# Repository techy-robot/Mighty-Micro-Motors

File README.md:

# Mighty Micro Motors
My goal with this project is to recreate the expensive and highly advanced motors typically found in big robots, such as in Boston Dynamics or MIT's robots, but at a **much** smaller scale. These are essentially tiny drone motors with a high reduction gearbox, a magnetic encoder, and a FOC controller board.

You can check out my project log [here](Progress%20Log.md).

This project is sponsored by [PCBWay](https://www.pcbway.com/)

## Gearbox
This has to be a resin printed or precision machined gearbox, just from the sheer smallness of everything. The brushless drone motors (HappyModel SE0802) are 10mm in diameter, so the gearbox ideally should be a similar size.

I'm currently thinking about having a cycloidal or split-ring planetary gearbox, due to the compact size and high reduction ratios

Preliminary CAD designs are on onshape, you can watch my progress here: [Mighty Micro Motors - Onshape](https://cad.onshape.com/documents/c861ec30af8169cf9c14bd7f/w/e538486c85e6a5fe77cd1d33/e/19bd07544dbaacbeb2fafd06). Step files and STL files will also be uploaded to this repo.

### Cycloidal 16-to-1 reduction:

Currently the design is twice as big as my ideal, with a 19mm diameter. I can not reduce the diameter without removing the bearings, possible reducing the lifespan. This *really* needs to be smaller, so I may do some testing and just remove some bearings. I'm not actually sure how well the 1x3x1mm bearings roll compared to just a smooth shaft. I could also cut the hole count down if the screws were also the shafts.

In real life:

### Split Ring Compound Planetary gearbox 74.66-to-1 reduction:

This goes by a variety of names, but basically this is a two-stage planetary gearbox, with the planets merged together. Due to some interesting mechanics, this type of gearbox can have **an extreme** reduction ratio in a relatively small size. The reduction ratio is the first stage ratio(ring teeth / sun teeth) multiplied by 2nd stage ring teeth, divided by the number of planets (simplified, this only works if both planet gear sets have the same number of teeth). The 2nd stage is advanced by a few teeth every revolution of the first. This operates on the same principle as a cycloidal drive and a harmonic drive, but with the added reduction ratio of the planetary gears, and without the vibration.

One thing to note with this type of gearbox is that the output encoder wires cannot fit through the center like my other gearbox, which limits the usable motion range to 270 degrees.

My particular version is a 74.66:1, in a much smaller form-factor than my cycloidal drive!

## Control board
### Version 1
My first version of the control board is designed to test all functions that may exist on a robot. I have the motor driver, a MCU for the algorithms, connectors for sensors (I2c and SPI), and a power management system.

A lot of care has been taken to design for EMI, which is why I have separate ground planes and have plotted current return paths for *most* traces. When I design a controller that supports 3+ motors I'm going to deal with length matching too on the low speed signals (Currently I'm testing all possible pin combinations, which doesn't lend itself to length matching). I'm still learning about good EMI design practices though, so there may be a big flaw in the design I don't see.

At it's current state the control PCB has been assembled and power tested. Nothing blew up or heated up, though I have discovered that the battery protection chip is not working. I will probably just bypass that circuit and move on.

[Schematic](Media/stm32g070%20and%20DRV8311%20single%20motor%20board%20-%20V1%20Alpha.pdf)

**Specs:**
- TI BQ25060 single-cell battery charger along with a BQ298012 battery protection chip. 
- 4 mosfets on board to control system power, 60+ amps of current
- TI DRV8311 motor driver, which can drive a brushless motor at 5 amps current (I fully expect heat problems due to the small size of the chip!)
- STM32G070CB, clocked at the max 64mhz (16mhz crystal scaled internally). 128kb mem, 64kb ram. The stm32 I chose is relatively inexpensive and *should be able to handle 3 motors*. (this was proven false later after testing other MCUs)

The motor driver section is 16x11mm, which hopefully is small enough and easily tileable for a small robot controller with lots of motors. The biggest part of the board is the power management, followed by the stm32.

**Ordering info**
The pcb is a 4 layer board, with 1 oz copper. Also, it is **strongly recommended** to order a stencil for both PCBs and to do a good job pasting the board. I fortunately ordered a stencil for the controller, but I put too much solder paste on and had to fix a lot of bridges after the fact. For the encoder board I manually pasted it, and that was a real pain to do a tiny QFN chip.

#### Tested functionality:
- Can be powered on without exploding
- 3.3v regulator on the motor chip works (though with a flaw that requires a kickstart to get it going)
- Can be programmed and flash an LED
- Can be clocked to a max 64mhz
- Power mosfet switching works on the charger
- Can communicate over SPI, UART and the debug interface
- Can drive a brushless drone motor at 10k rpm

#### Photos

Assembled:

(Note that I messed up on the mosfets I ordered which were too tiny. I have the correct mosfet specified now)

### Version 2
My second test control board has had a lot of the components switched, and actually split the DRV8311 onto a separate board.

I am testing a lot of the same functionality as last time, and its still a single motor system.

[Schematic](Kicad/esp32-s3%20single%20motor%20&%20battery%20controller/esp32-s3%20single%20motor%20&%20battery%20controller.pdf)

**Specs:**
- TI BQ24780S 2-cell battery charger along with a BQ276905 battery balancer, monitor, and protection chip. 
- 2 power mosfets on board to control system power, 60+ amps of current, 4 additional smaller mosfets for charging
- ESP32-S3 microcontroller, clocked at 240mhz and can support 4 motors (not in this version)
- TI DRV8311 controlling the motor, except on a separate PCB located on the back of the motor.
- 7 pin FPC connector for the V2 encoder

#### Photos

Off board controller

## Encoder board

This is a little magnetic board I designed to be attached to the end of the motor. It has a MA735 chip, which is low cost and seemed perfect for my needs. The resolution is inversely proportional to rotational reading speeds, so I will be fine no matter which end of the gearbox I stick it on. Low resolution on the high-speed end will mean I still have high resolution positioning on the output, and high resolution on the output side is fine because the output is slower.

The board is barely bigger than the jst sh connector on top for SPI communication! V2 of the board is mounted on a flex cable so it doesn't need wires.

The encoder chips datasheet recommends a diametrically magnetized 5x3mm neodymium magnet to operate. I used a 6x3mm from K&J magnetics: [D42DIA](https://www.kjmagnetics.com/proddetail.asp?prod=D42DIA).

## Sponsorship

Thanks to PCBWay for reaching out to sponsor my project. They kindly offered to allow me to test their pcb manufacturing capabilites with this project.

I liked the quality of the pcbs I received for the V2 boards, everything was soldered correctly with only minor burn marks on the through-hole components. The assembly service they offered was also top-notch, much easier than hand assembling at home. When I made a mistake on one of the PCB assemblies I ordered, they were quick to ask what should be done, and were willing to let me have the misplaced parts (sot-23 transitors instead of sot23-5) so I could fix it myself with some bodge wires. The one downside to PCBway is the cost of the boards, I would not normally pay for prototype pcbs at their prices.

Try them out if you haven't [https://www.pcbway.com/](https://www.pcbway.com/).

See the section **Version 2/Photos** above for pictures.

## Code
There is not that much code currently, just some tests to verify the board and motors work, and a programmer definition for my Flipper Zero. I am planning on using the wonderful [SimpleFOC](https://github.com/simplefoc/Arduino-FOC) library as a starting point for the motor control, building out my own communication protocol or going with ROS 2 style communication. I may also add some motor control algorithms as I discover more.

I have tuned the PID algorithms for my particular HappyModel SE0802 brushless drone motors.

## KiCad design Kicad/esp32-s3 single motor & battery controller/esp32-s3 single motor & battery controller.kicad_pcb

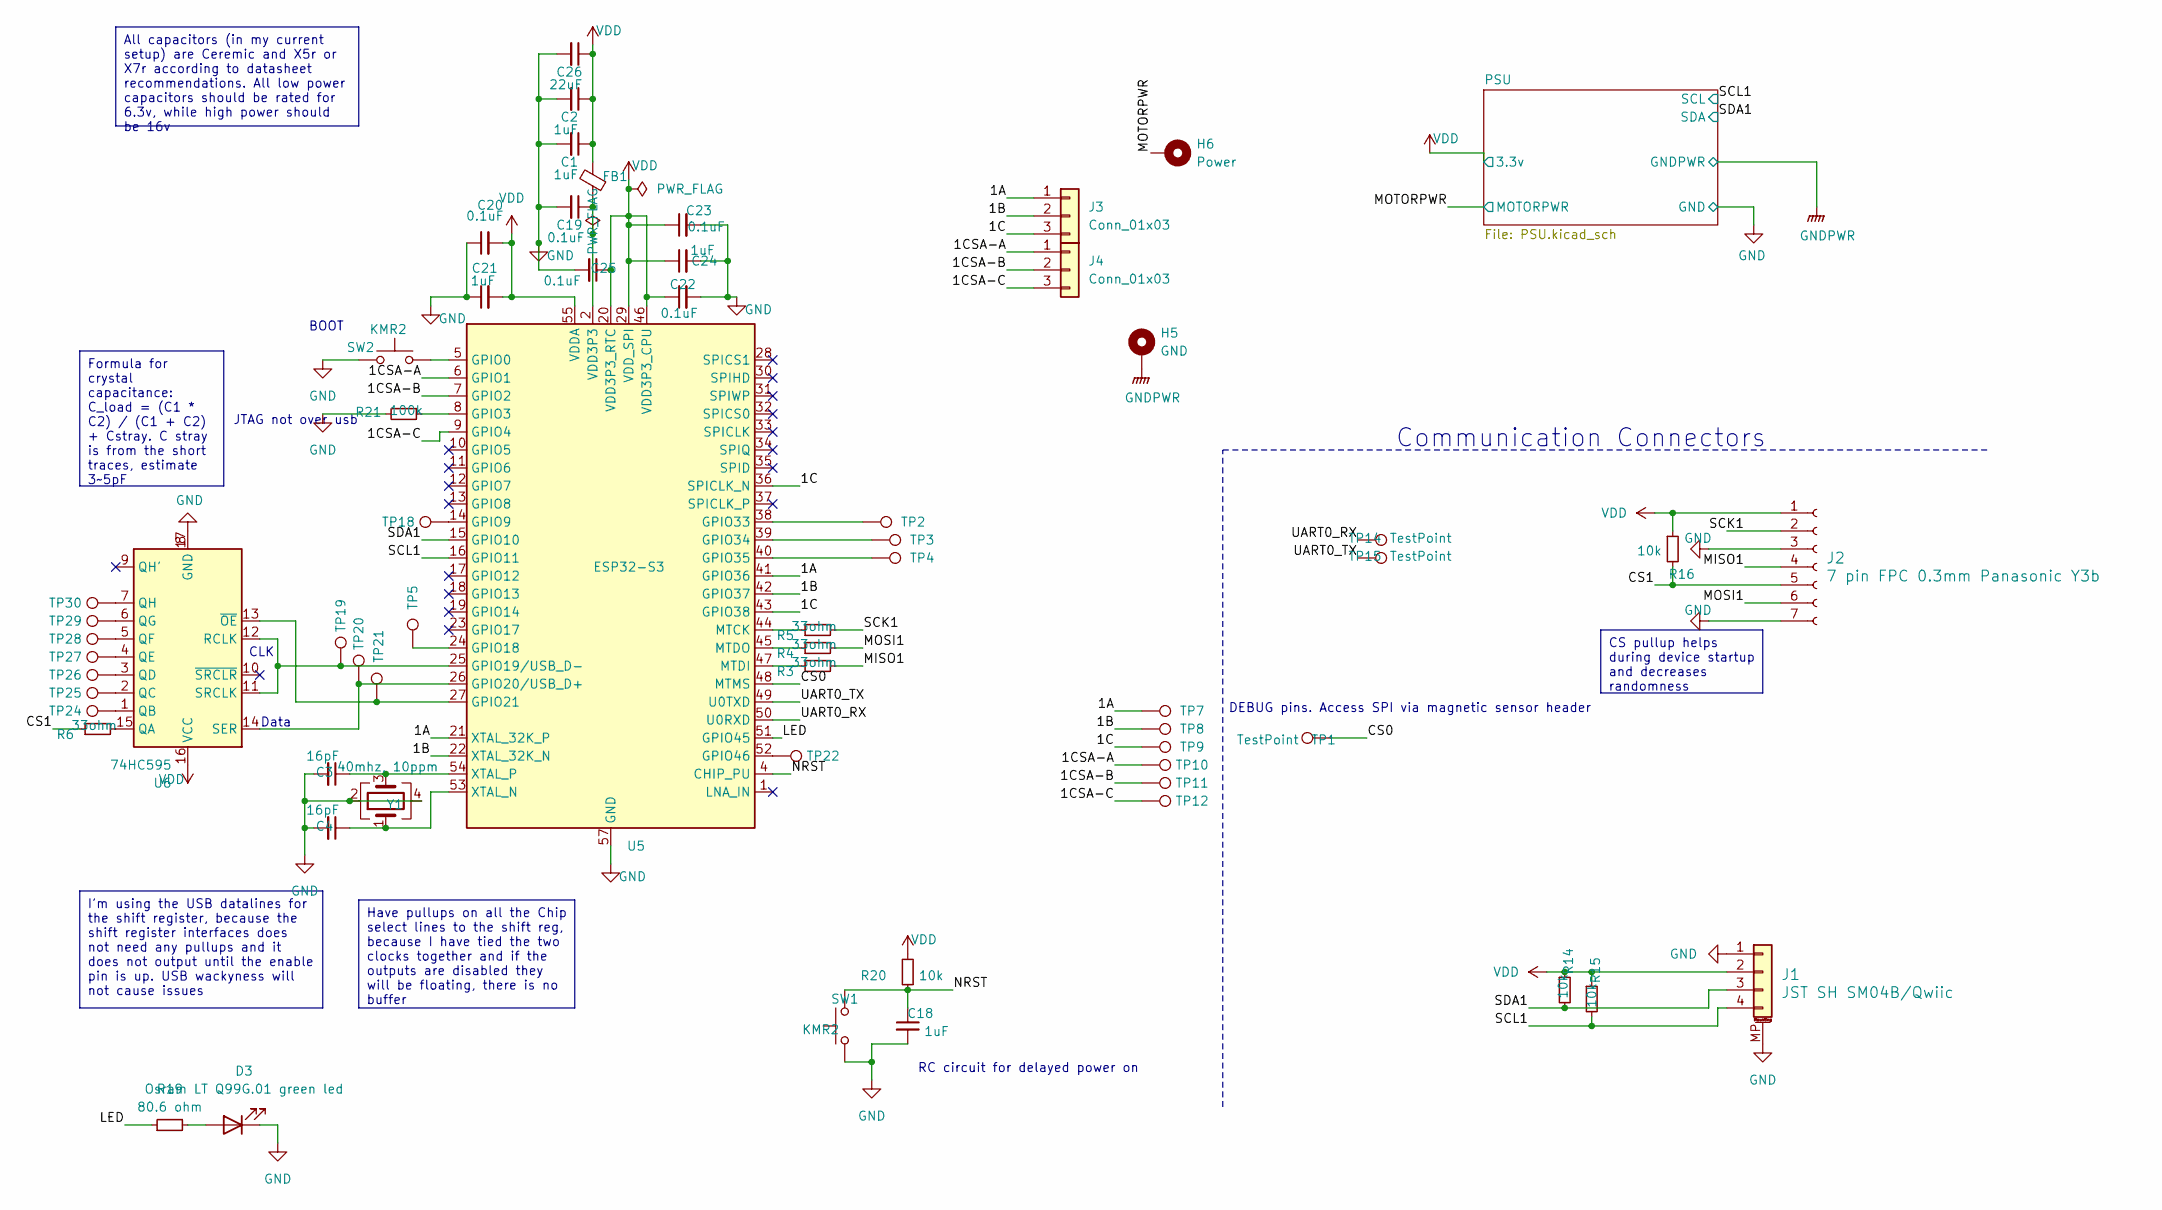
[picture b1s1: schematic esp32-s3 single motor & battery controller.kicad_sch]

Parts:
C1, C2, C21, C24: 1uF; C_0603_1608Metric
C3, C4: 16pF; C_0603_1608Metric_Pad1.08x0.95mm_HandSolder
C18: 1uF; C_0603_1608Metric_Pad1.08x0.95mm_HandSolder
C19, C20, C22, C23, C25: 0.1uF; C_0603_1608Metric
C26: 22uF; C_0603_1608Metric
D3: Osram LT Q99G.01 green led; LED_0603_1608Metric_Pad1.05x0.95mm_HandSolder
FB1: 120ohm imp @100mhz; L_0603_1608Metric
H5: GND; TestPoint_Pad_D2.0mm
H6: Power; TestPoint_Pad_D2.0mm
J1: JST SH SM04B/Qwiic; JST_SH_SM04B-SRSS-TB_1x04-1MP_P1.00mm_Horizontal
J2: 7 pin FPC 0.3mm Panasonic Y3b; fpc_7pin_0.3mm_connector Panasonic
J3, J4: Conn_01x03; PinHeader_1x03_P1.27mm_Vertical
R3, R4, R5, R6: 33ohm; R_0603_1608Metric
R14, R15, R16, R20: 10k; R_0603_1608Metric
R19: 80.6 ohm; R_0603_1608Metric
R21: 100k; R_0603_1608Metric
SW1, SW2: KMR2; SW_Push_1P1T_NO_CK_KMR2
TP1, TP14, TP15: TestPoint; TestPoint_Pad_D1.0mm
TP2, TP3, TP4, TP5, TP7, TP8, TP9, TP10, TP11, TP12, TP18, TP19, TP20, TP21, TP22, TP24, TP25, TP26, TP27, TP28, TP29, TP30: TestPoint_Pad_D1.0mm
U5: ESP32-S3; QFN-56-1EP_7x7mm_P0.4mm_EP4x4mm
U6: 74HC595; DHVQFN-16-1EP_2.5x3.5mm_P0.5mm_EP1x2mm
Y1: 40mhz, 10ppm; Crystal_SMD_3225-4Pin_3.2x2.5mm

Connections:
/1A: J3.1, TP7.1, U5.21 (XTAL_32K_P), U5.41 (GPIO36)
/1B: J3.2, TP8.1, U5.22 (XTAL_32K_N), U5.42 (GPIO37)
/1C: J3.3, TP9.1, U5.36 (SPICLK_N), U5.43 (GPIO38)
/1CSA-A: J4.1, TP10.1, U5.6 (GPIO1)
/1CSA-B: J4.2, TP11.1, U5.7 (GPIO2)
/1CSA-C: J4.3, TP12.1, U5.9 (GPIO4)
/CS0: TP1.1, U5.48 (MTMS)
/CS1: J2.5, R6.1, R16.2
/LED: R19.1, U5.51 (GPIO45)
/MISO1: J2.4, R3.2
/MOSI1: J2.6, R4.2
/MOTORPWR: H6.1; also elsewhere on the board
/NRST: C18.1, R20.1, SW1.2, U5.4 (CHIP_PU)
/SCK1: J2.2, R5.2
/SCL1: J1.4, R15.2, U5.16 (GPIO11); also elsewhere on the board
/SDA1: J1.3, R14.2, U5.15 (GPIO10); also elsewhere on the board
/UART0_RX: TP14.1, U5.50 (U0RXD)
/UART0_TX: TP15.1, U5.49 (U0TXD)
GND: C1.2, C2.2, C3.2, C4.2, C18.2, C19.2, C20.1, C21.1, C22.2, C23.2, C24.2, C25.2, C26.2, D3.1 (K), J1.1, J1.MP (MountPin), J2.3, J2.7, R21.2, SW1.1, SW2.1, U5.57 (GND), U6.8 (GND), U6.17 (GND), Y1.2, Y1.4; also elsewhere on the board
GNDPWR: H5.1; also elsewhere on the board
unnamed: C19.1, FB1.1, U5.2 (VDD3P3), U5.3 (VDD3P3)
unnamed: D3.2 (A), R19.2
unnamed: SW2.2, U5.5 (GPIO0)
unnamed: R21.1, U5.8 (GPIO3)
unnamed: TP18.1, U5.14 (GPIO9)
unnamed: TP5.1, U5.24 (GPIO18)
unnamed: TP19.1, U5.25 (GPIO19/USB_D-), U6.11 (SRCLK), U6.12 (RCLK)
unnamed: TP20.1, U5.26 (GPIO20/USB_D+), U6.14 (SER)
unnamed: TP21.1, U5.27 (GPIO21), U6.13 (~OE)
unnamed: TP2.1, U5.38 (GPIO33)
unnamed: TP3.1, U5.39 (GPIO34)
unnamed: TP4.1, U5.40 (GPIO35)
unnamed: TP22.1, U5.52 (GPIO46)
unnamed: R5.1, U5.44 (MTCK)
unnamed: R3.1, U5.47 (MTDI)
unnamed: R4.1, U5.45 (MTDO)
unnamed: C4.1, U5.53 (XTAL_N), Y1.1
unnamed: C3.1, U5.54 (XTAL_P), Y1.3
unnamed: R6.2, U6.15 (QA)
unnamed: TP24.1, U6.1 (QB)
unnamed: TP25.1, U6.2 (QC)
unnamed: TP26.1, U6.3 (QD)
unnamed: TP27.1, U6.4 (QE)
unnamed: TP28.1, U6.5 (QF)
unnamed: TP29.1, U6.6 (QG)
unnamed: TP30.1, U6.7 (QH)
VDD: C1.1, C2.1, C20.2, C21.2, C22.1, C23.1, C24.1, C25.1, C26.1, FB1.2, J1.2, J2.1, R14.1, R15.1, R16.1, R20.2, U5.20 (VDD3P3_RTC), U5.29 (VDD_SPI), U5.46 (VDD3P3_CPU), U5.55 (VDDA), U5.56 (VDDA), U6.16 (VCC); also elsewhere on the board

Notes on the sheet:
CS pullup helps during device startup and decreases randomness
All capacitors (in my current setup) are Ceremic and X5r or X7r according to datasheet recommendations. All low power capacitors should be rated for 6.3v, while high power should be 16v
Formula for crystal capacitance: C_load = (C1 * C2) / (C1 + C2) + Cstray. C stray is from the short traces, estimate 3~5pF
Have pullups on all the Chip select lines to the shift reg, because I have tied the two clocks together and if the outputs are disabled they will be floating, there is no buffer
I'm using the USB datalines for the shift register, because the shift register interfaces does not need any pullups and it does not output until the enable pin is up. USB wackyness will not cause issues
Communication Connectors
JTAG not over usb
RC circuit for delayed power on
Data
BOOT
CLK
DEBUG pins. Access SPI via magnetic sensor header

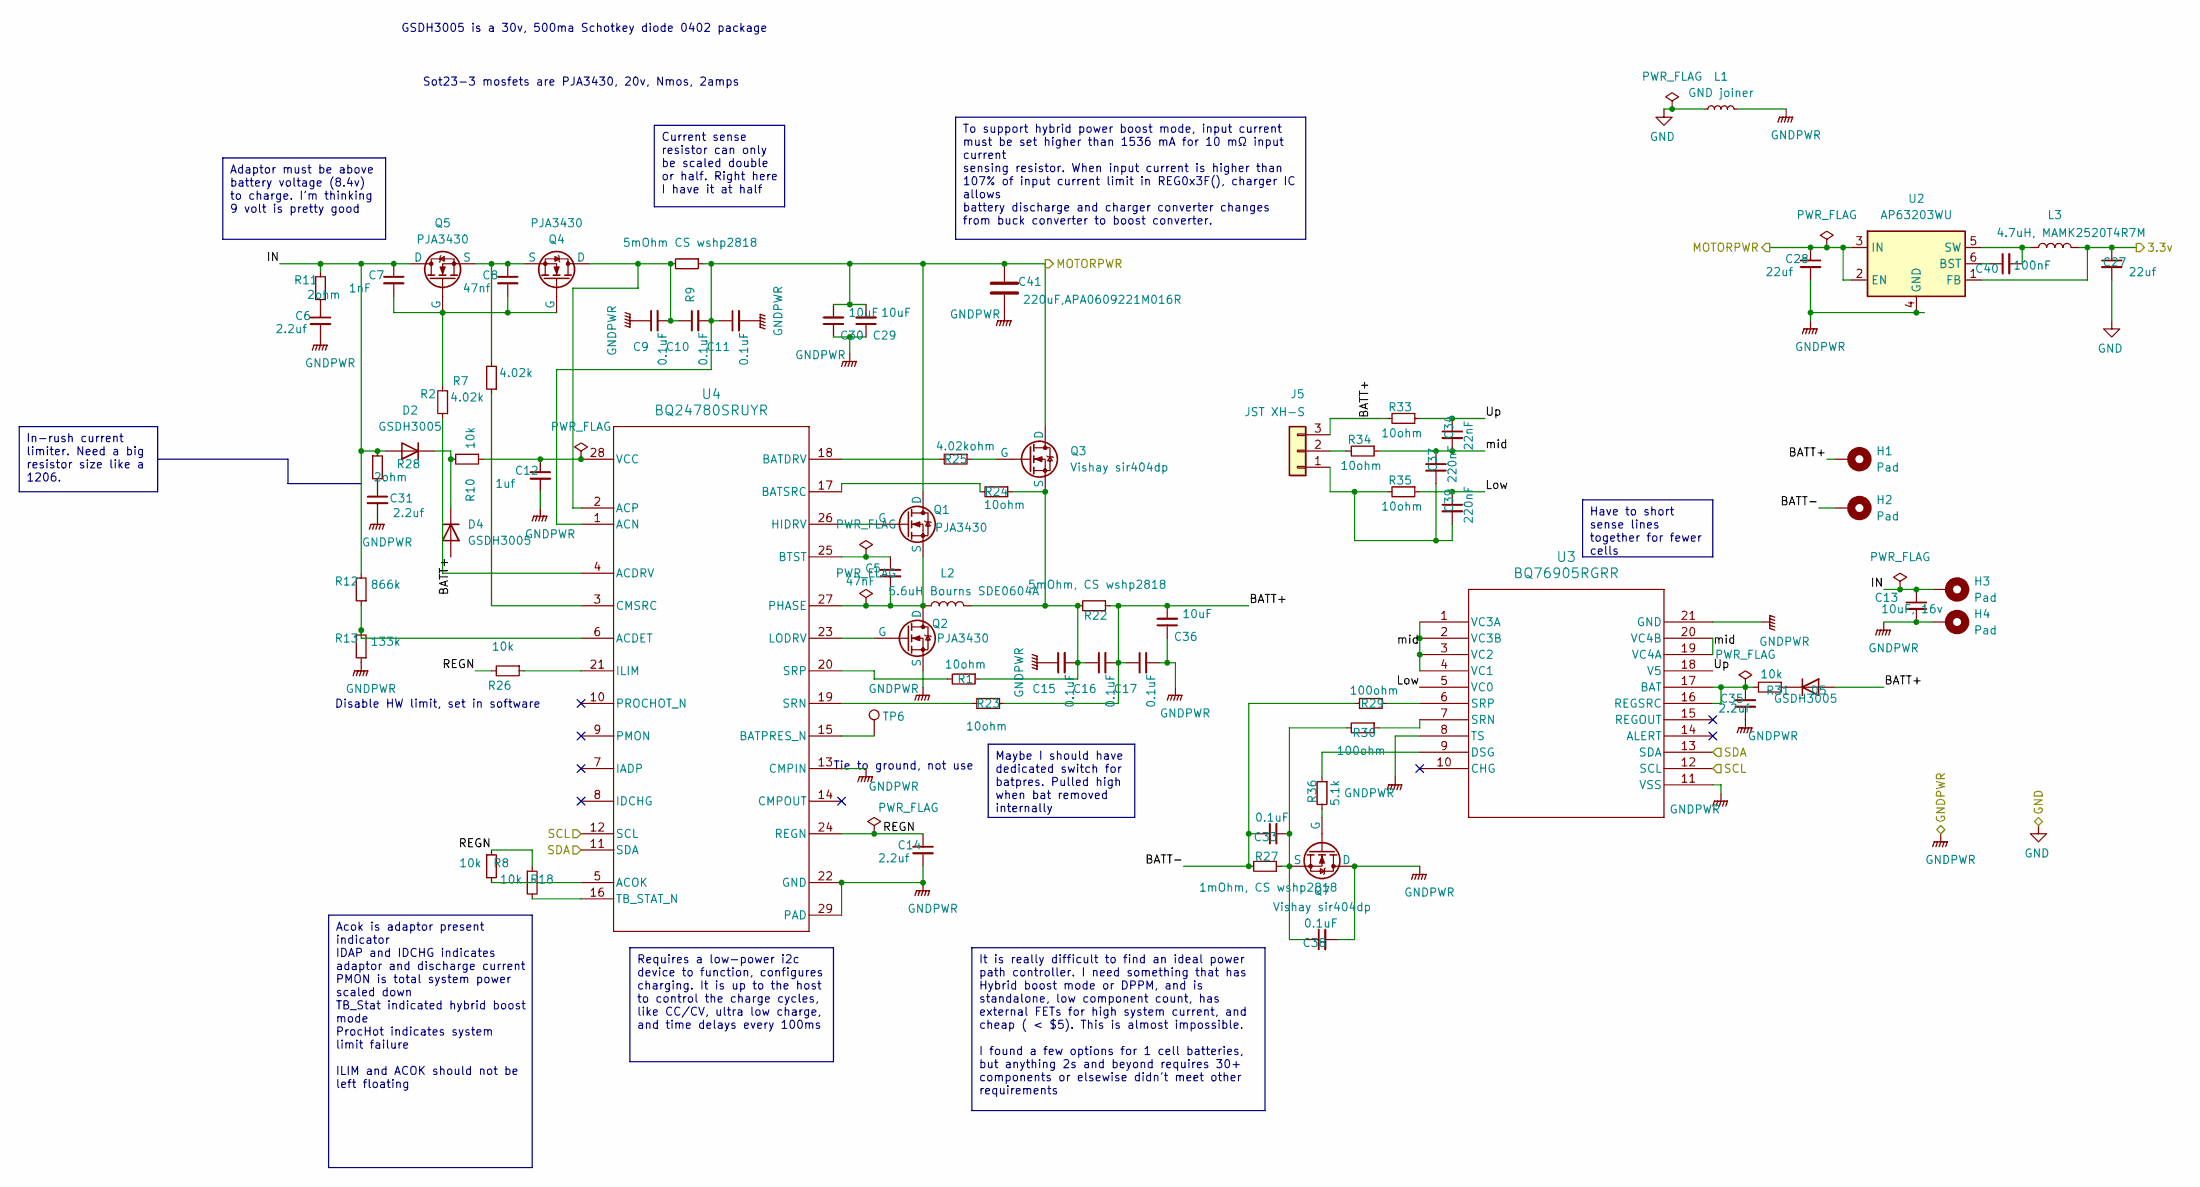
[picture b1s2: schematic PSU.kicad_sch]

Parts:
C5: 47nF; C_0603_1608Metric
C6, C14, C31, C35: 2.2uf; C_0603_1608Metric
C7: 1nF; C_0603_1608Metric
C8: 47nf; C_0603_1608Metric
C9, C10, C11, C15, C16, C17, C33, C38: 0.1uF; C_0603_1608Metric
C12: 1uf; C_0603_1608Metric
C13: 10uF, 16v; C_0603_1608Metric_Pad1.08x0.95mm_HandSolder
C27, C28: 22uf; C_0603_1608Metric
C29, C30, C36: 10uF; C_0603_1608Metric
C34: 22nF; C_0603_1608Metric
C37, C39: 220nF; C_0603_1608Metric
C40: 100nF; C_0603_1608Metric
C41: 220uF,APA0609221M016R; CP_Elec_6.3x9.9
D2, D4, D5: GSDH3005; D_0402_1005Metric
H1, H2, H3, H4: Pad; TestPoint_Pad_3.0x3.0mm
J5: JST XH-S; JST_XH_S3B-XH-A_1x03_P2.50mm_Horizontal
L1: GND joiner; SolderJumper-2_P1.3mm_Bridged_Pad1.0x1.5mm
L2: 5.6uH Bourns SDE0604A; L_Bourns_SDR0604
L3: 4.7uH, MAMK2520T4R7M; L_1008_2520Metric
Q1, Q2, Q4, Q5: PJA3430; SOT-323_SC-70
Q3, Q7: Vishay sir404dp; PQFN-8-EP_6x5mm_P1.27mm_Generic
R1, R23, R24, R33, R34, R35: 10ohm; R_0603_1608Metric
R2, R7: 4.02k; R_0603_1608Metric
R8, R10, R18, R26, R31: 10k; R_0603_1608Metric
R9: 5mOhm CS wshp2818; R_2816_7142Metric
R11, R28: 2ohm; R_0603_1608Metric
R12: 866k; R_0603_1608Metric
R13: 133k; R_0603_1608Metric
R22: 5mOhm, CS wshp2818; R_2816_7142Metric
R25: 4.02kohm; R_0603_1608Metric
R27: 1mOhm, CS wshp2818; R_2816_7142Metric
R29, R30: 100ohm; R_0603_1608Metric
R36: 5.1k; R_0603_1608Metric
TP6: TestPoint_Pad_D1.0mm
U2: AP63203WU; TSOT-23-6
U3: BQ76905RGRR; VQFN20_RGR_TEX
U4: BQ24780SRUYR; RUY0028A

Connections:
/MOTORPWR: C10.2, C11.1, C28.1, C29.2, C30.2, C41.1, Q1.1 (D), Q3.1 (D), Q3.2 (D), Q3.3 (D), R9.1, U2.2 (EN), U2.3 (IN), U4.1 (ACN); also elsewhere on the board
/PSU/BATT+: C16.2, C17.1, C36.2, D4.2 (A), D5.2 (A), H1.1, J5.3, R22.1, R23.1, R33.2
/PSU/BATT-: C33.1, H2.1, R27.2, R29.2
/PSU/IN: C7.1, C13.1, D2.2 (A), H3.1, Q5.1 (D), R11.2, R12.2, R28.1
/PSU/Low: C39.1, R35.1, U3.5 (VC0)
/PSU/REGN: C14.1, R8.1, R18.1, R26.2, U4.24 (REGN)
/PSU/Up: C34.1, R33.1, U3.18 (V5)
/PSU/mid: C34.2, C37.1, R34.1, U3.1 (VC3A), U3.2 (VC3B), U3.3 (VC2), U3.4 (VC1), U3.19 (VC4A), U3.20 (VC4B)
/SCL1: U3.12 (SCL), U4.12 (SCL); also elsewhere on the board
/SDA1: U3.13 (SDA), U4.11 (SDA); also elsewhere on the board
GND: C27.2, L1.1; also elsewhere on the board
GNDPWR: C6.2, C9.1, C11.2, C12.2, C13.2, C14.2, C15.1, C17.2, C28.2, C29.1, C30.1, C31.2, C35.2, C36.1, C38.2, C41.2, H4.1, L1.2, Q2.3 (S), Q7.1 (D), Q7.2 (D), Q7.3 (D), R13.1, U2.4 (GND), U3.8 (TS), U3.11 (VSS), U3.21 (GND), U4.13 (CMPIN), U4.22 (GND), U4.29 (PAD); also elsewhere on the board
unnamed: C6.1, R11.1
unnamed: C31.1, R28.2
unnamed: D2.1 (K), D4.1 (K), R10.2
unnamed: D5.1 (K), R31.1
unnamed: C37.2, C39.2, J5.1, R35.2
unnamed: J5.2, R34.2
unnamed: Q1.2 (G), U4.26 (HIDRV)
unnamed: C5.2, L2.1, Q1.3 (S), Q2.1 (D), U4.27 (PHASE)
unnamed: Q2.2 (G), U4.23 (LODRV)
unnamed: Q3.4 (G), R25.1
unnamed: C15.2, C16.1, L2.2, Q3.5 (S), R1.1, R22.2, R24.1
unnamed: C9.2, C10.1, Q4.1 (D), R9.2, U4.2 (ACP)
unnamed: C7.2, C8.2, Q4.2 (G), Q5.2 (G), R2.2
unnamed: C8.1, Q4.3 (S), Q5.3 (S), R7.2
unnamed: Q7.4 (G), R36.2
unnamed: C33.2, C38.1, Q7.5 (S), R27.1, R30.2
unnamed: C40.1, U2.6 (BST)
unnamed: C40.2, L3.1, U2.5 (SW)
unnamed: C35.1, R31.2, U3.16 (REGSRC), U3.17 (BAT)
unnamed: R36.1, U3.9 (DSG)
unnamed: R30.1, U3.7 (SRN)
unnamed: R29.1, U3.6 (SRP)
unnamed: R12.1, R13.2, U4.6 (ACDET)
unnamed: R2.1, U4.4 (ACDRV)
unnamed: R8.2, U4.5 (ACOK)
unnamed: R25.2, U4.18 (BATDRV)
unnamed: TP6.1, U4.15 (BATPRES_N)
unnamed: R24.2, U4.17 (BATSRC)
unnamed: C5.1, U4.25 (BTST)
unnamed: R7.1, U4.3 (CMSRC)
unnamed: R26.1, U4.21 (ILIM)
unnamed: R23.2, U4.19 (SRN)
unnamed: R1.2, U4.20 (SRP)
unnamed: R18.2, U4.16 (TB_STAT_N)
unnamed: C12.1, R10.1, U4.28 (VCC)
VDD: C27.1, L3.2, U2.1 (FB); also elsewhere on the board

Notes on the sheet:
It is really difficult to find an ideal power path controller. I need something that has Hybrid boost mode or DPPM, and is standalone, low component count, has external FETs for high system current, and cheap ( < $5). This is almost impossible. I found a few options for 1 cell batteries, but anythi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
Adaptor must be above battery voltage (8.4v) to charge. I'm thinking 9 volt is pretty good
Maybe I should have dedicated switch for batpres. Pulled high when bat removed internally
In-rush current limiter. Need a big resistor size like a 1206.
Requires a low-power i2c device to function, configures charging. It is up to the host to control the charge cycles, like CC/CV, ultra low charge, and time delays every 100ms
Current sense resistor can only be scaled double or half. Right here I have it at half
To support hybrid power boost mode, input current must be set higher than 1536 mA for 10 mΩ input current sensing resistor. When input current is higher than 107% of input current limit in REG0x3F(), charger IC allows battery discharge and charger converter changes from buck converter to boost conv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
Have to short sense lines together for fewer cells
Acok is adaptor present indicator IDAP and IDCHG indicates adaptor and discharge current PMON is total system power scaled down TB_Stat indicated hybrid boost mode ProcHot indicates system limit failure ILIM and ACOK should not be left floating
Sot23-3 mosfets are PJA3430, 20v, Nmos, 2amps
Tie to ground, not use
Disable HW limit, set in software
GSDH3005 is a 30v, 500ma Schotkey diode 0402 package

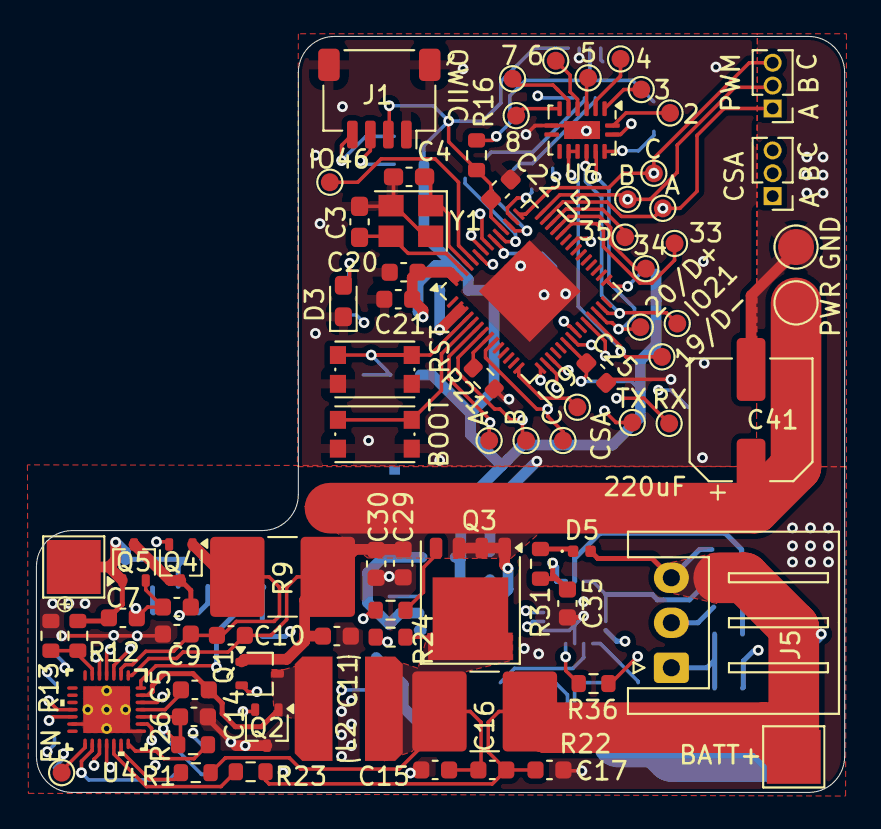
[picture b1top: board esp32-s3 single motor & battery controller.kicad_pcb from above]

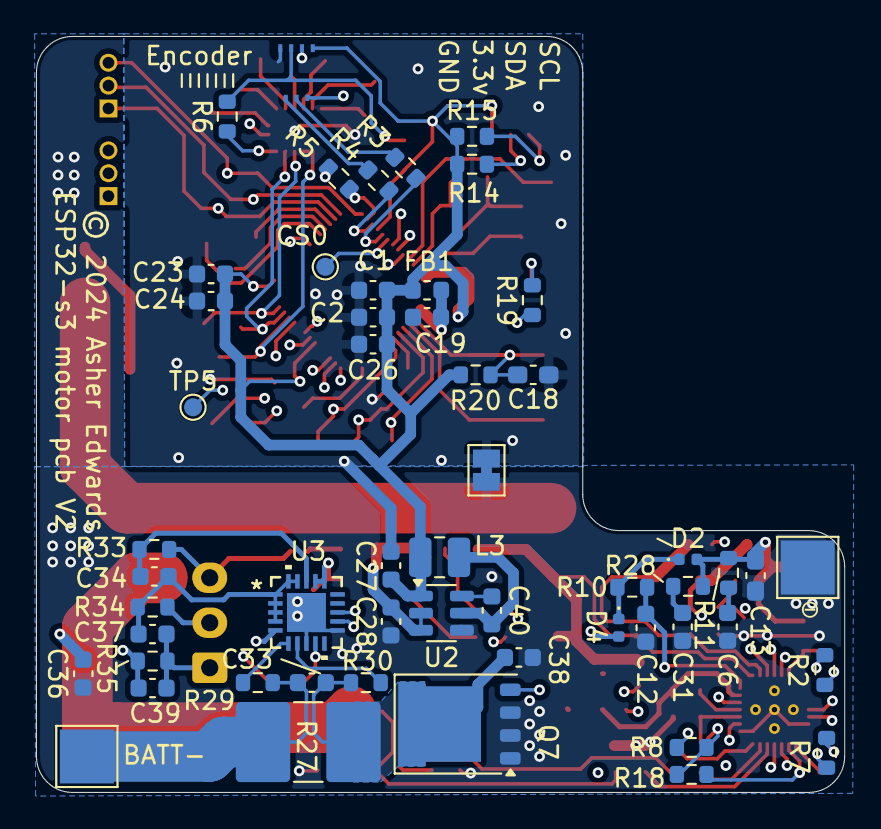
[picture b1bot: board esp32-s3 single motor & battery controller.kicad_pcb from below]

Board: 4 copper layers, 44.9 x 42.0 mm, 133 parts (54 on the bottom side), 89 nets.

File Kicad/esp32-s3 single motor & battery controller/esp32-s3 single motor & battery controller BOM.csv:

"Id";"Designator";"Footprint";"Quantity";"Designation";"Supplier and ref";
1;"C3,C4";"C_0603_1608Metric_Pad1.08x0.95mm_HandSolder";2;"16pF";;;
2;"Y1";"Crystal_SMD_3225-4Pin_3.2x2.5mm";1;"40mhz, 10ppm";;;
3;"C9,C15,C16,C10,C25,C20,C11,C22,C17,C33,C23,C38,C19";"C_0603_1608Metric";13;"0.1uF";;;
4;"J4,J3";"PinHeader_1x03_P1.27mm_Vertical";2;"Conn_01x03";;;
5;"R24,R1,R23,R35,R33,R34";"R_0603_1608Metric";6;"10ohm";;;
6;"C21,C2,C1,C24";"C_0603_1608Metric";4;"1uF";;;
7;"R26,R16,R31,R10,R14,R20,R8,R18,R15";"R_0603_1608Metric";9;"10k";;;
8;"J1";"JST_SH_SM04B-SRSS-TB_1x04-1MP_P1.00mm_Horizontal";1;"JST SH SM04B/Qwiic";;;
9;"TP3,TP2,TP18,TP4,TP22";"TestPoint_Pad_D1.0mm";5;"~";;;
10;"R21";"R_0603_1608Metric";1;"100k";;;
11;"R9";"R_2816_7142Metric";1;"5mOhm CS wshp2818";;;
12;"D3";"LED_0603_1608Metric_Pad1.05x0.95mm_HandSolder";1;"Osram LT Q99G.01 green led";;;
13;"Q1,Q5,Q4,Q2";"SOT-323_SC-70";4;"PJA3430";;;
14;"R25";"R_0603_1608Metric";1;"4.02kohm";;;
15;"U4";"RUY0028A";1;"BQ24780SRUYR";;;
16;"C5";"C_0603_1608Metric";1;"47nF";;;
17;"SW2,SW1";"SW_Push_1P1T_NO_CK_KMR2";2;"KMR2";;;
18;"L2";"L_Bourns_SDR0604";1;"5.6uH Bourns SDE0604A";;;
19;"J5";"JST_XH_S3B-XH-A_1x03_P2.50mm_Horizontal";1;"JST XH-S";;;
20;"C8";"C_0603_1608Metric";1;"47nf";;;
21;"C41";"CP_Elec_6.3x9.9";1;"220uF,APA0609221M016R";;;
22;"U5";"QFN-56-1EP_7x7mm_P0.4mm_EP4x4mm";1;"ESP32-S3";;;
23;"C14,C35,C6,C31";"C_0603_1608Metric";4;"2.2uf";;;
24;"Q3,Q7";"PQFN-8-EP_6x5mm_P1.27mm_Generic";2;"Vishay sir404dp";;;
25;"R12";"R_0603_1608Metric";1;"866k";;;
26;"C29,C30,C36";"C_0603_1608Metric";3;"10uF";;;
27;"D5,D2,D4";"D_0402_1005Metric";3;"GSDH3005";;;
28;"R13";"R_0603_1608Metric";1;"133k";;;
29;"U6";"DHVQFN-16-1EP_2.5x3.5mm_P0.5mm_EP1x2mm";1;"74HC595";;;
30;"C7";"C_0603_1608Metric";1;"1nF";;;
31;"R22";"R_2816_7142Metric";1;"5mOhm, CS wshp2818";;;
32;"R36";"R_0603_1608Metric";1;"5.1k";;;
33;"R11,R28";"R_0603_1608Metric";2;"2ohm";;;
34;"L1";"SolderJumper-2_P1.3mm_Bridged_Pad1.0x1.5mm";1;"GND joiner";;;
35;"R4,R5,R3,R6";"R_0603_1608Metric";4;"33ohm";;;
36;"C28,C27";"C_0603_1608Metric";2;"22uf";;;
37;"C40";"C_0603_1608Metric";1;"100nF";;;
38;"C34";"C_0603_1608Metric";1;"22nF";;;
39;"C13";"C_0603_1608Metric_Pad1.08x0.95mm_HandSolder";1;"10uF, 16v";;;
40;"L3";"L_1008_2520Metric";1;"4.7uH, MAMK2520T4R7M";;;
41;"C39,C37";"C_0603_1608Metric";2;"220nF";;;
42;"C26";"C_0603_1608Metric";1;"22uF";;;
43;"C12";"C_0603_1608Metric";1;"1uf";;;
44;"C18";"C_0603_1608Metric_Pad1.08x0.95mm_HandSolder";1;"1uF";;;
45;"R29,R30";"R_0603_1608Metric";2;"100ohm";;;
46;"R27";"R_2816_7142Metric";1;"1mOhm, CS wshp2818";;;
47;"R2,R7";"R_0603_1608Metric";2;"4.02k";;;
48;"J2";"fpc_7pin_0.3mm_connector Panasonic";1;"7 pin FPC 0.3mm Panasonic Y3b";;;
49;"FB1";"L_0603_1608Metric";1;"120ohm imp @100mhz";;;
50;"U3";"VQFN20_RGR_TEX";1;"BQ76905RGRR";;;
51;"U2";"TSOT-23-6";1;"AP63203WU";;;
52;"R19";"R_0603_1608Metric";1;"80.6 ohm";;;

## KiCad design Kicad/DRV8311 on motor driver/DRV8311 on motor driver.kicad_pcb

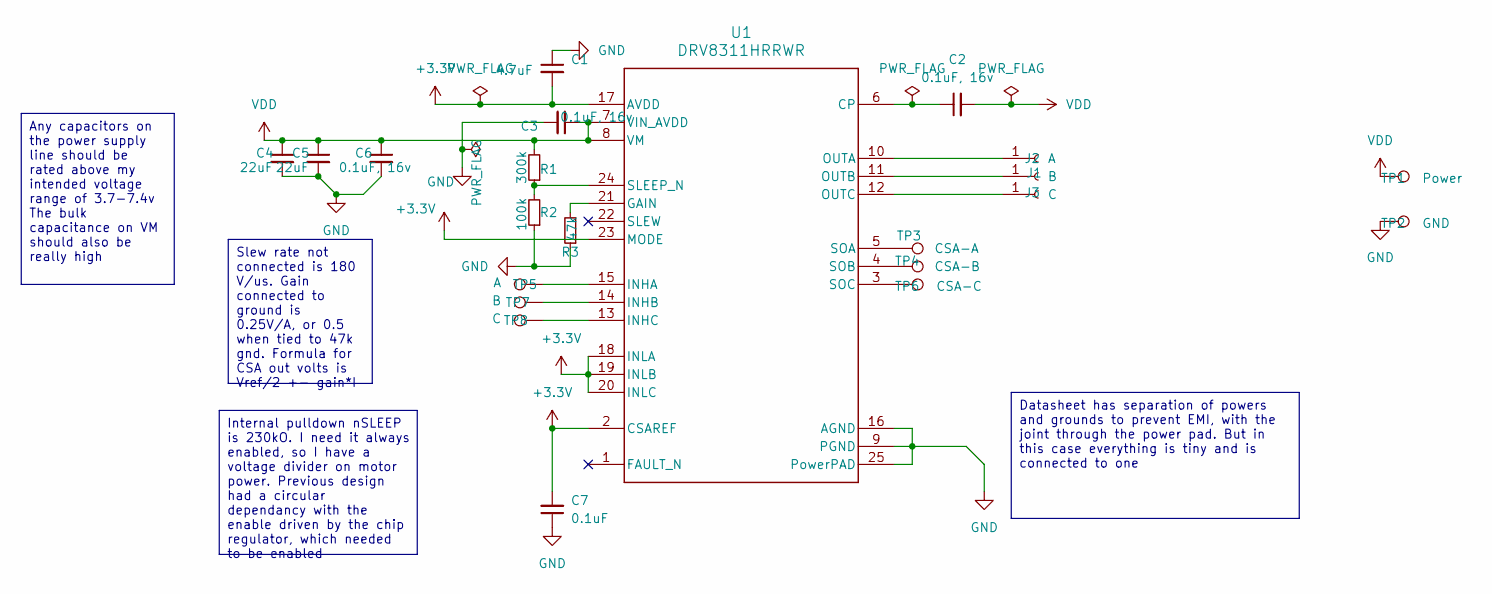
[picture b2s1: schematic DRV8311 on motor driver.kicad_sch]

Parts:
C1: 4.7uF; C_0402_1005Metric
C2, C3, C6: 0.1uF, 16v; C_0402_1005Metric
C4, C5: 22uF; C_0402_1005Metric
C7: 0.1uF; C_0402_1005Metric
J1: B; PinHeader_1x01_P1.27mm_Round
J2: A; PinHeader_1x01_P1.27mm_Round
J3: C; PinHeader_1x01_P1.27mm_Round
R1: 300k; R_0402_1005Metric
R2: 100k; R_0402_1005Metric
R3: 47k; R_0402_1005Metric
TP1: Power; TestPoint_Pad_D2.0mm
TP2: GND; TestPoint_Pad_D2.0mm
TP3: CSA-A; TestPoint_Pad_D1.0mm
TP4: CSA-B; TestPoint_Pad_D1.0mm
TP5: A; TestPoint_Pad_D1.0mm
TP6: CSA-C; TestPoint_Pad_D1.0mm
TP7: B; TestPoint_Pad_D1.0mm
TP8: C; TestPoint_Pad_D1.0mm
U1: DRV8311HRRWR; DRV8311_0.3mmVias

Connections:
+3.3V: C1.2, C7.2, U1.2 (CSAREF), U1.17 (AVDD), U1.18 (INLA), U1.19 (INLB), U1.20 (INLC), U1.23 (MODE)
GND: C1.1, C3.2, C4.2, C5.2, C6.2, C7.1, R2.1, R3.1, TP2.1, U1.9 (PGND), U1.16 (AGND), U1.25 (PowerPAD)
unnamed: J1.1, U1.11 (OUTB)
unnamed: J2.1, U1.10 (OUTA)
unnamed: J3.1, U1.12 (OUTC)
unnamed: C2.1, U1.6 (CP)
unnamed: R3.2, U1.21 (GAIN)
unnamed: TP5.1, U1.15 (INHA)
unnamed: TP7.1, U1.14 (INHB)
unnamed: TP8.1, U1.13 (INHC)
unnamed: R1.1, R2.2, U1.24 (SLEEP_N)
unnamed: TP3.1, U1.5 (SOA)
unnamed: TP4.1, U1.4 (SOB)
unnamed: TP6.1, U1.3 (SOC)
VDD: C2.2, C3.1, C4.1, C5.1, C6.1, R1.2, TP1.1, U1.7 (VIN_AVDD), U1.8 (VM)

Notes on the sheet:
Internal pulldown nSLEEP is 230kO. I need it always enabled, so I have a voltage divider on motor power. Previous design had a circular dependancy with the enable driven by the chip regulator, which needed to be enabled
Slew rate not connected is 180 V/us. Gain connected to ground is 0.25V/A, or 0.5 when tied to 47k gnd. Formula for CSA out volts is Vref/2 +- gain*I
Datasheet has separation of powers and grounds to prevent EMI, with the joint through the power pad. But in this case everything is tiny and is connected to one
Any capacitors on the power supply line should be rated above my intended voltage range of 3.7-7.4v The bulk capacitance on VM should also be really high

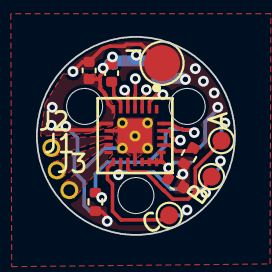
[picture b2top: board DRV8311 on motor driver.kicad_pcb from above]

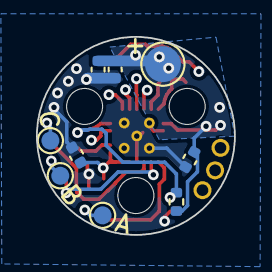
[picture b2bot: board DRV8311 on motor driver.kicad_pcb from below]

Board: 4 copper layers, 11.0 x 11.0 mm, 22 parts (9 on the bottom side), 15 nets.

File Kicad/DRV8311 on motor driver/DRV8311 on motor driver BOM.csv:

"Id";"Designator";"Footprint";"Quantity";"Designation";"Supplier and ref";
1;"C1";"C_0402_1005Metric";1;"4.7uF";;;
2;"C3,C2,C6";"C_0402_1005Metric";3;"0.1uF, 16v";;;
3;"U1";"DRV8311_0.3mmVias";1;"DRV8311HRRWR";;;
4;"R3";"R_0402_1005Metric";1;"47k";;;
5;"R2";"R_0402_1005Metric";1;"100k";;;
6;"R1";"R_0402_1005Metric";1;"300k";;;
7;"C7";"C_0402_1005Metric";1;"0.1uF";;;
8;"C5,C4";"C_0402_1005Metric";2;"22uF";;;

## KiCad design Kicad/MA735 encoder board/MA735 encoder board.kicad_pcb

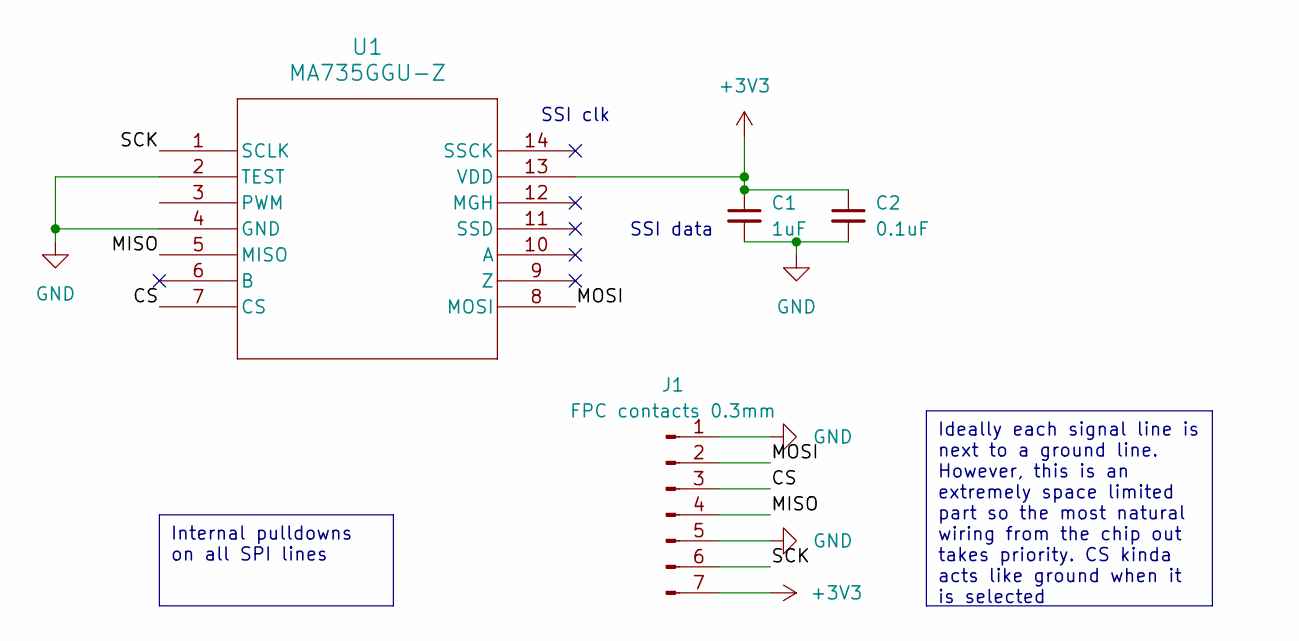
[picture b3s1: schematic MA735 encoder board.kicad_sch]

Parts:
C1: 1uF; C_0402_1005Metric
C2: 0.1uF; C_0402_1005Metric
J1: FPC contacts 0.3mm; 7pin_fpc_contact_0.3mmptich
U1: MA735GGU-Z; UTQFN-14_MA735_MNP

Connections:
+3V3: C1.1, C2.1, J1.7, U1.13 (VDD)
/CS: J1.3, U1.7 (CS)
/MISO: J1.4, U1.5 (MISO)
/MOSI: J1.2, U1.8 (MOSI)
/SCK: J1.6, U1.1 (SCLK)
GND: C1.2, C2.2, J1.1, J1.5, U1.2 (TEST), U1.4 (GND)

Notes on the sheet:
Ideally each signal line is next to a ground line. However, this is an extremely space limited part so the most natural wiring from the chip out takes priority. CS kinda acts like ground when it is selected
Internal pulldowns on all SPI lines
SSI clk
SSI data

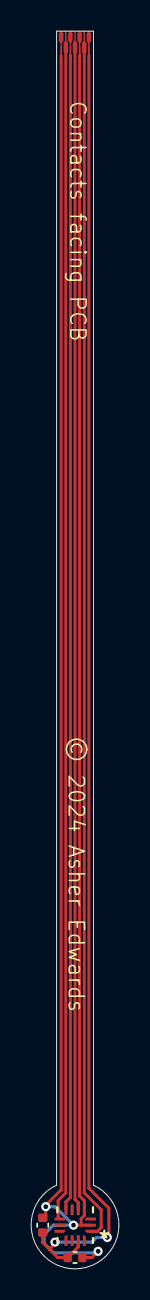
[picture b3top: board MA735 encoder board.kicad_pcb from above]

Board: 2 copper layers, 5.7 x 80.4 mm, 4 parts (0 on the bottom side), 6 nets.

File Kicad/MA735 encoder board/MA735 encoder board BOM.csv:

"Id";"Designator";"Footprint";"Quantity";"Designation";"Supplier and ref";
1;"U1";"UTQFN-14_MA735_MNP";1;"MA735GGU-Z";;;
2;"C2";"C_0402_1005Metric";1;"0.1uF";;;
3;"C1";"C_0402_1005Metric";1;"1uF";;;

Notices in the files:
Kicad/MA735 encoder board/MA735 encoder board.kicad_pcb:
© 2024 Asher Edwards
Kicad/stm32g070 and DRV8311 single motor board - V1 Alpha/stm32g070 and DRV8311 single motor board - V1 Alpha.kicad_pcb:
© 2024 Asher James Edwards
